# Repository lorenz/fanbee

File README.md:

# FanBee :honeybee:
*A Zigbee-controlled 140mm fan with electronically-controlled valve*

Skip to the Build Guide if you want to know how to build one.

# Introduction

## User Interface
The small LED (D3) near the reset button indicates if the lowest (MCU) power
rail has power. If it is not illuminated nothing will happen, check power rails.

The firmware initially starts blinking its status LED (D4, near the JTAG
header) every 2 seconds, indicating that it is idle and is not connected to any
network. Press the Pair button after your ZigBee network is ready to join a new
device. The status LED will start to blink rapidly (every 0.5s) until it has
joined a network, then it will turn off.

Pressing the pair button while the device is already joined to a network will
result in two quick flashes of the status LED.

Long-pressing the pair button (>5s) will reset the device.

The last LED (D5) indicates if the fan is currently powered. It can be used
to diagnose fan or connectivity issues.

## Coordinator compatibility
Because the ZigBee HVAC fan device type is unfit for this device (it supports
various modes but no speed control) I've opted to implement it as a generic
level-controlled device (just like dimmable lights). This should give it fairly
broad coordinator compatibility.

There's a device model for the FanBee in Zigbee2MQTT which is what I'm
personally using to control them.

## Notes
* The power connector is designed for daisy-chaining, that's why there are
  two positive and negative positions. Only one of each needs to be connected
  for normal operation.
* Second Servo output is not used currently, was used in an earlier revision
  and left for any future use as there was space.
* SPI flash can be left unpopulated if you don't ever want to use OTA updates
  or maybe a later (larger) firmware. It's currently unused.
* Newer TI SDKs have been tested but drop off the Zigbee network for unknown
  reasons after hours or days. Use the pinned version.
* Make sure that the surface your're installing the base plate on is flat.
  Otherwise the bell shape gets distorted and the butterfly valve disk gets
  stuck. The tolerances there need to be relatively tight to not allow too much
  air to go through in closed state.

# Build Guide
## Requirements

### Off-the-shelf hardware
| Quantity | Part description |
| -------- | ---------------- |
| 8        | M3 brass heat-set inserts |
| 1        | M3 15mm buttonhead fastener |
| 1        | M3 10mm buttonhead fastener |
| 4        | M3 5mm fastener (ideally with integrated washer) |
| 4        | M4 countersunk fasteners for attaching the housing |
| 2        | 10x15x4mm ball bearings |
| 1        | SG90-compatible 180° servo |
| 1        | 140mm 24V or 12V PC-compatible PWM fan (plus screws if not included) |
| 30cm     | 2GT timing belt (open-loop) |

This was designed for the Noctua NF-A14 industrialPPC-24V-3000 SP IP67 PWM, but
any other electrically-compatible 24V or 12V fans can be used. Note that the
power supply voltage needs to match the fan voltage, there is no regulator for
the fan power supply.

### PCB
The control PCB is custom-designed and can be ordered at your favorite PCB
manufacturer in various states of assembly. All SMT parts can be assembled
for relatively cheap by JLCPCB. One PCB is needed for each FanBee.

A OpenOCD and JTAG compatible programmer with a 2.45mm ARM 10 Pin JTAG
connector is required. This has been tested with a generic FT2232 board, but
a TI XDS110 or compatible LaunchPad should also work.

### Printed parts
The STLs for all printed parts are in the `parts` folder. One of each is
needed for a single fanbee.
`servo_pulley.stl` should be printed in resin or with a 0.2mm nozzle, the
rest of the parts do not need to be as precise.

## Assembly steps
1. Insert the 4 heat-set inserts into the studs for holding the PCB.
2. Insert the two heat-set inserts into the base for holding an optional PCB enclosure.
3. Insert a heat-set insert each into the bottom and top holes of the valve disk.
4. Press both ball bearings into their housings on the main part.
5. Place the fan at the back, route the wires through the slot and attach it with four fan screws.
6. Route the servo cables through the hole and attach the servo with two screws.
7. Attach the PCB with four 5mm screws.
8. Connect the 4-pin fan connector and 3-pin servo connector.
9. Place the fan disk between the bearings and push in the retaining pin from the bottom and the disk pulley from the top.
10. Secure the retaining pin with the 10mm M3 screw.
11. Secure the disk pulley with the 15mm M3 screw.
12. Push the servo pulley onto the servo and secure it with the provided screw.
13. Cut a sufficiently-long section of belt, loop it around the two servos and secure both ends with the belt retainer.
15. Attach the JTAG programmer and temporary power and flash the firmware.

## Future work
* Public CI for firmware and manufacturing files
* Render/photos of the finished product

# License
MIT for all the code I wrote as well as the CAD design files. Some code is also
related to TI's SimpleLink SDK (especially the generated syscfg), I don't claim
ownership of that, but TI grants you relatively broad permissions for most use.

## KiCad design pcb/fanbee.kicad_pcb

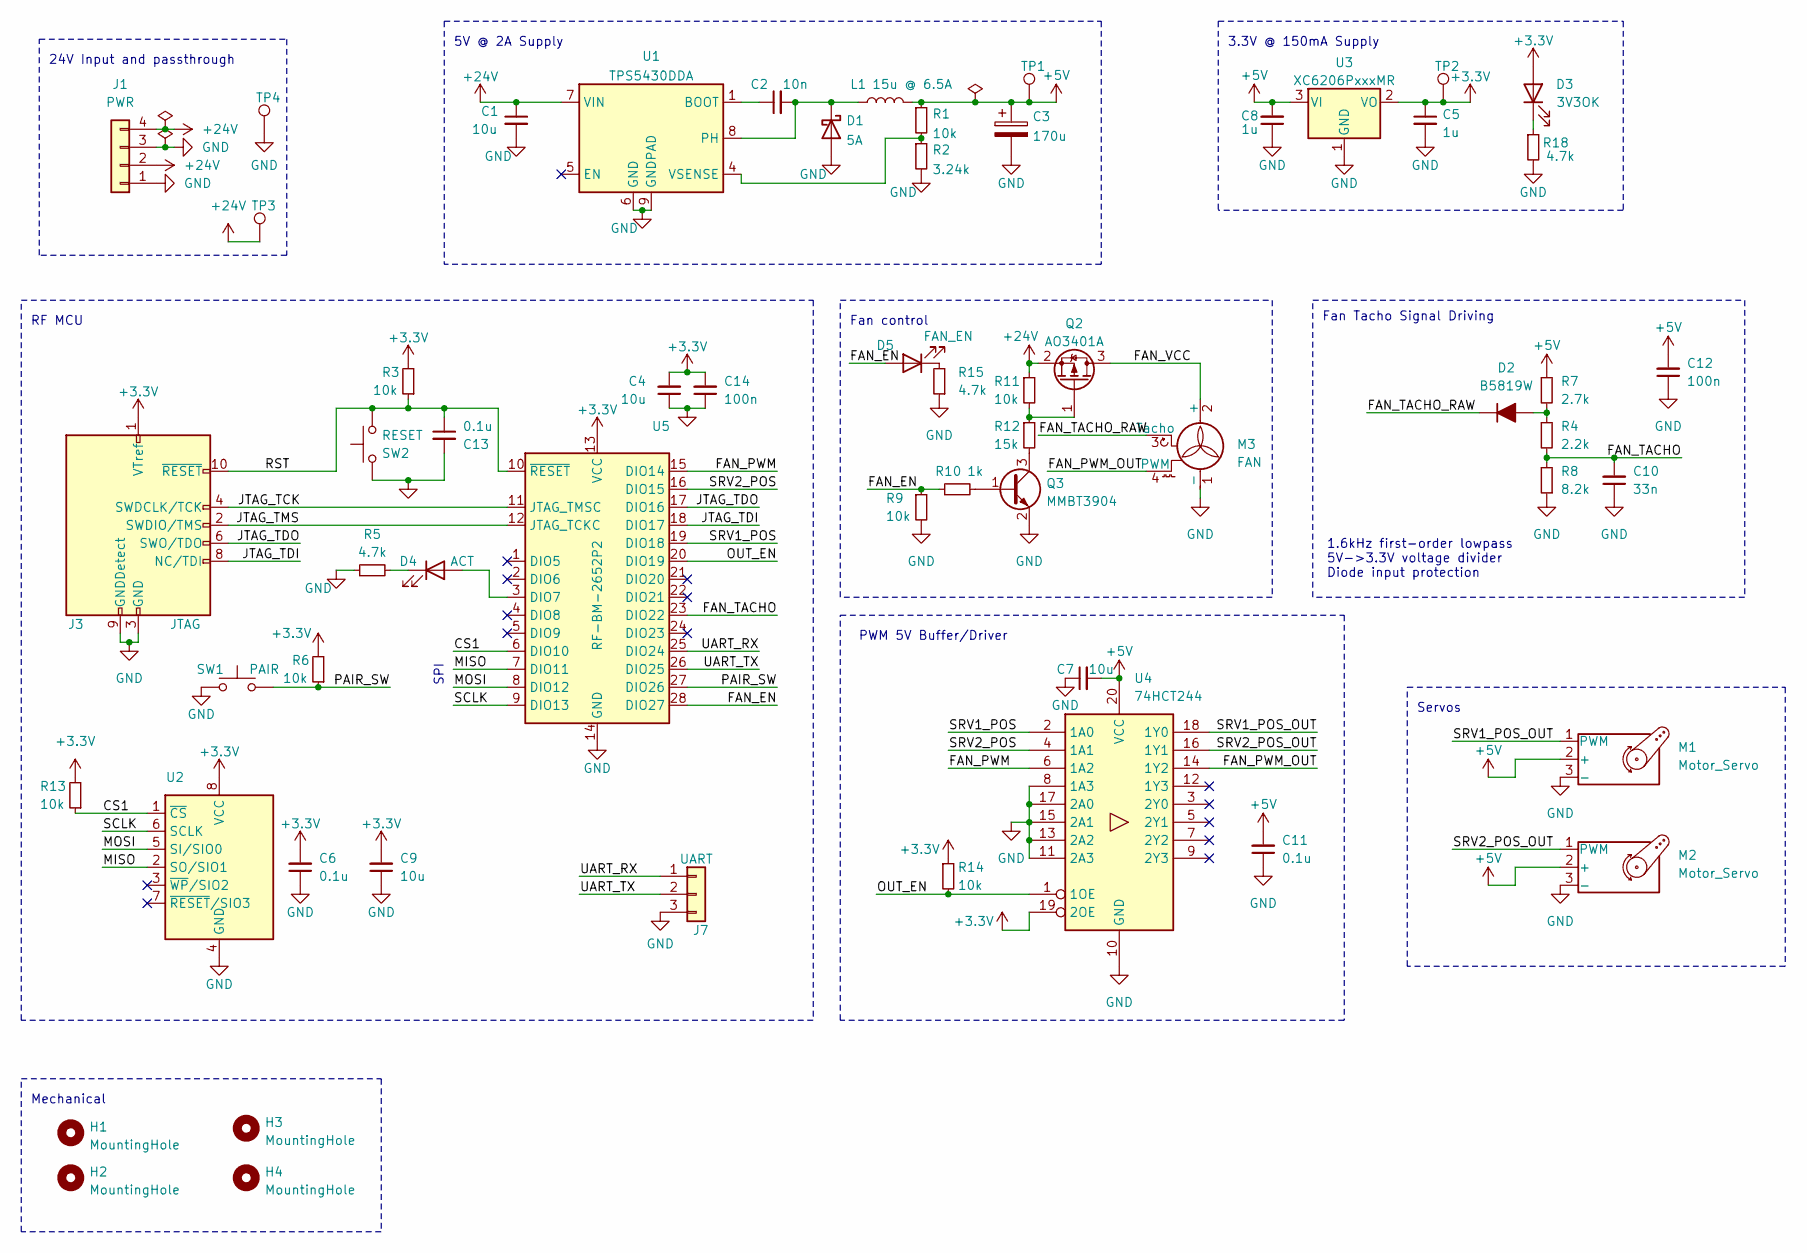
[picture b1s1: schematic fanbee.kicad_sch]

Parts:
C1, C4, C7, C9: 10u; C_0805_2012Metric; LCSC C440198
C2: 10n; C_0402_1005Metric; LCSC C15195
C3: 170u; CP_Elec_6.3x5.9; LCSC C311623
C5, C8: 1u; C_0805_2012Metric; LCSC C28323
C6, C11, C13: 0.1u; C_0402_1005Metric; LCSC C1525
C10: 33n; C_0603_1608Metric; LCSC C21117
C12, C14: 100n; C_0603_1608Metric; LCSC C14663
D1: 5A; D_SMA; LCSC C22452
D2: B5819W; D_SOD-123; LCSC C8598
D3: 3V3OK; LED_0805_2012Metric; LCSC C2297
D4: ACT; LED_0805_2012Metric; LCSC C2297
D5: FAN_EN; LED_0805_2012Metric; LCSC C2297
H1, H2, H3, H4: MountingHole; MountingHole_3.2mm_M3
J1: PWR; PhoenixContact_MCV_1,5_4-G-3.81_1x04_P3.81mm_Vertical; LCSC C8410
J3: JTAG; PinHeader_2x05_P2.54mm_Vertical; LCSC C7501276
J7: UART; PinHeader_1x03_P2.54mm_Vertical; LCSC C7501581
L1: 15u @ 6.5A; L_Sunlord_MWSA1004_11.5x10.5mm; LCSC C151872
M1, M2: Motor_Servo; PinHeader_1x03_P2.54mm_Vertical; LCSC C7501581
M3: FAN; FanPinHeader_1x04_P2.54mm_Vertical; LCSC C7501582
Q2: AO3401A; SOT-23; LCSC C15127
Q3: MMBT3904; SOT-23; LCSC C20526
R1, R3, R6, R9, R11, R13, R14: 10k; R_0402_1005Metric; LCSC C25744
R2: 3.24k; R_0402_1005Metric; LCSC C22994
R4: 2.2k; R_0402_1005Metric; LCSC C25879
R5, R15, R18: 4.7k; R_0402_1005Metric; LCSC C25900
R7: 2.7k; R_0603_1608Metric; LCSC C13167
R8: 8.2k; R_0402_1005Metric; LCSC C25924
R10: 1k; R_0402_1005Metric; LCSC C11702
R12: 15k; R_0402_1005Metric; LCSC C25756
SW1: PAIR; SW_SPST_TL3342; LCSC C318884
SW2: RESET; SW_SPST_TL3342; LCSC C318884
TP1, TP2, TP3, TP4: TestPoint; TestPoint_Pad_D1.0mm
U1: TPS5430DDA; TI_SO-PowerPAD-8_ThermalVias; LCSC C9864
U2: Macronix_USON8_EP_2x3_Pitch0.5mm; LCSC C152596
U3: XC6206PxxxMR; SOT-23-3; LCSC C5446
U4: 74HCT244; TSSOP-20_4.4x6.5mm_P0.65mm; LCSC C131088
U5: RF-BM-2652P2; LCSC C5440064

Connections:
+3.3V: C4.2, C5.1, C6.2, C9.2, C14.2, D3.2 (A), J3.1 (VTref), R3.2, R6.2, R13.2, R14.1, TP2.1, U2.8 (VCC), U3.2 (VO), U4.19 (2OE), U5.13 (VCC)
+5V: C3.1, C7.2, C8.2, C11.2, C12.2, L1.2, M1.2 (+), M2.2 (+), R1.1, R7.1, TP1.1, U3.3 (VI), U4.20 (VCC)
+24V: C1.1, J1.2, J1.4, Q2.2 (S), R11.1, TP3.1, U1.7 (VIN)
/CS1: R13.1, U2.1 (~CS), U5.6 (DIO10)
/FAN_EN: D5.2 (A), R9.1, R10.1, U5.28 (DIO27)
/FAN_PWM: U4.6 (1A2), U5.15 (DIO14)
/FAN_PWM_OUT: M3.4 (PWM), U4.14 (1Y2)
/FAN_TACHO: C10.2, R4.2, R8.2, U5.23 (DIO22)
/FAN_TACHO_RAW: D2.1 (K), M3.3 (Tacho)
/FAN_VCC: M3.2 (+), Q2.3 (D)
/JTAG_TCK: J3.4 (SWDCLK/TCK), U5.11 (JTAG_TMSC)
/JTAG_TDI: J3.8 (NC/TDI), U5.18 (DIO17)
/JTAG_TDO: J3.6 (SWO/TDO), U5.17 (DIO16)
/JTAG_TMS: J3.2 (SWDIO/TMS), U5.12 (JTAG_TCKC)
/MISO: U2.2 (SO/SIO1), U5.7 (DIO11)
/MOSI: U2.5 (SI/SIO0), U5.8 (DIO12)
/OUT_EN: R14.2, U4.1 (1OE), U5.20 (DIO19)
/PAIR_SW: R6.1, SW1.2, U5.27 (DIO26)
/RST: C13.1, J3.10 (~RESET), R3.1, SW2.1, U5.10 (~RESET)
/SCLK: U2.6 (SCLK), U5.9 (DIO13)
/SRV1_POS: U4.2 (1A0), U5.19 (DIO18)
/SRV1_POS_OUT: M1.1 (PWM), U4.18 (1Y0)
/SRV2_POS: U4.4 (1A1), U5.16 (DIO15)
/SRV2_POS_OUT: M2.1 (PWM), U4.16 (1Y1)
/UART_RX: J7.1, U5.25 (DIO24)
/UART_TX: J7.2, U5.26 (DIO25)
GND: C1.2, C3.2, C4.1, C5.2, C6.1, C7.1, C8.1, C9.1, C10.1, C11.1, C12.1, C13.2, C14.1, D1.2 (A), J1.1, J1.3, J3.3 (GND), J3.5 (GND), J3.9 (GNDDetect), J7.3, M1.3 (-), M2.3 (-), M3.1 (-), Q3.2 (E), R2.2, R5.1, R8.1, R9.2, R15.1, R18.2, SW1.1, SW2.2, TP4.1, U1.6 (GND), U1.9 (GNDPAD), U2.4 (GND), U2.EP (GND), U3.1 (GND), U4.8 (1A3), U4.10 (GND), U4.11 (2A3), U4.13 (2A2), U4.15 (2A1), U4.17 (2A0), U5.14 (GND)
unnamed: C2.2, D1.1 (K), L1.1, U1.8 (PH)
unnamed: D2.2 (A), R4.1, R7.2
unnamed: D3.1 (K), R18.1
unnamed: D4.2 (A), U5.3 (DIO7)
unnamed: D4.1 (K), R5.2
unnamed: D5.1 (K), R15.2
unnamed: Q2.1 (G), R11.2, R12.1
unnamed: Q3.1 (B), R10.2
unnamed: Q3.3 (C), R12.2
unnamed: C2.1, U1.1 (BOOT)
unnamed: R1.2, R2.1, U1.4 (VSENSE)

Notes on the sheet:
1.6kHz first-order lowpass 5V->3.3V voltage divider Diode input protection
RF MCU
SPI
Mechanical
Servos
5V @ 2A Supply
Fan Tacho Signal Driving
PWM 5V Buffer/Driver
24V Input and passthrough
Fan control
3.3V @ 150mA Supply

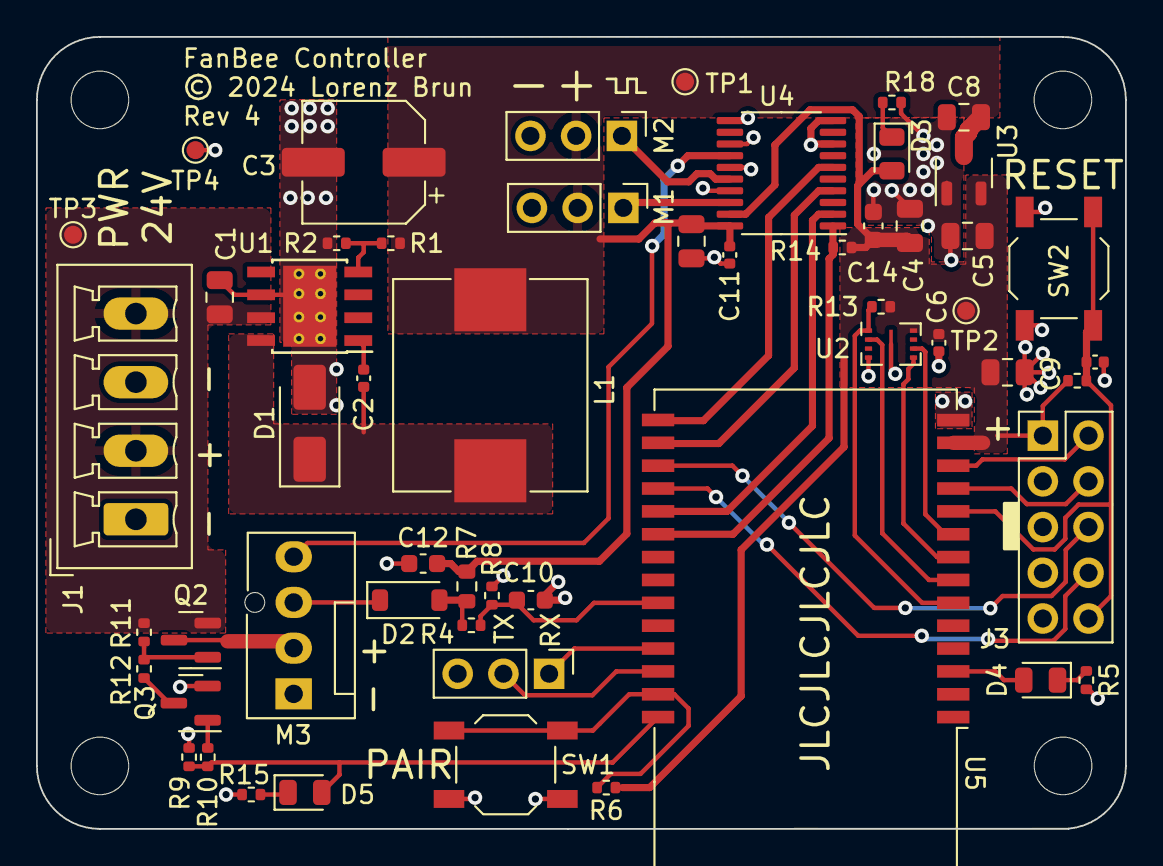
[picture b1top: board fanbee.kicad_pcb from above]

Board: 2 copper layers, 60.5 x 44.0 mm, 59 parts (0 on the bottom side), 38 nets.

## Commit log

2024-12-31 Initial public release
2025-03-09 Add product render to Readme

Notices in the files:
pcb/fanbee.kicad_pcb:
© 2024 Lorenz Brun
